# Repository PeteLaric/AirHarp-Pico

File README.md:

# AirHarp-Pico
A gestural autoharp that functions as a class-compliant USB MIDI controller instrument.

http://www.AirHarp.com

Originally conceived in 2010, the AirHarp is a gestural autoharp that allows the musician to strum chords on an invisible beam of ultrasound.  For several years, I manufactured and sold these musical instruments online.  The entire project is open source.  If you build one, please send me a note!  I'd love to see it.

Cheers,

~ Pete

http://www.PeteLaric.com

PeteLaric@protonmail.com

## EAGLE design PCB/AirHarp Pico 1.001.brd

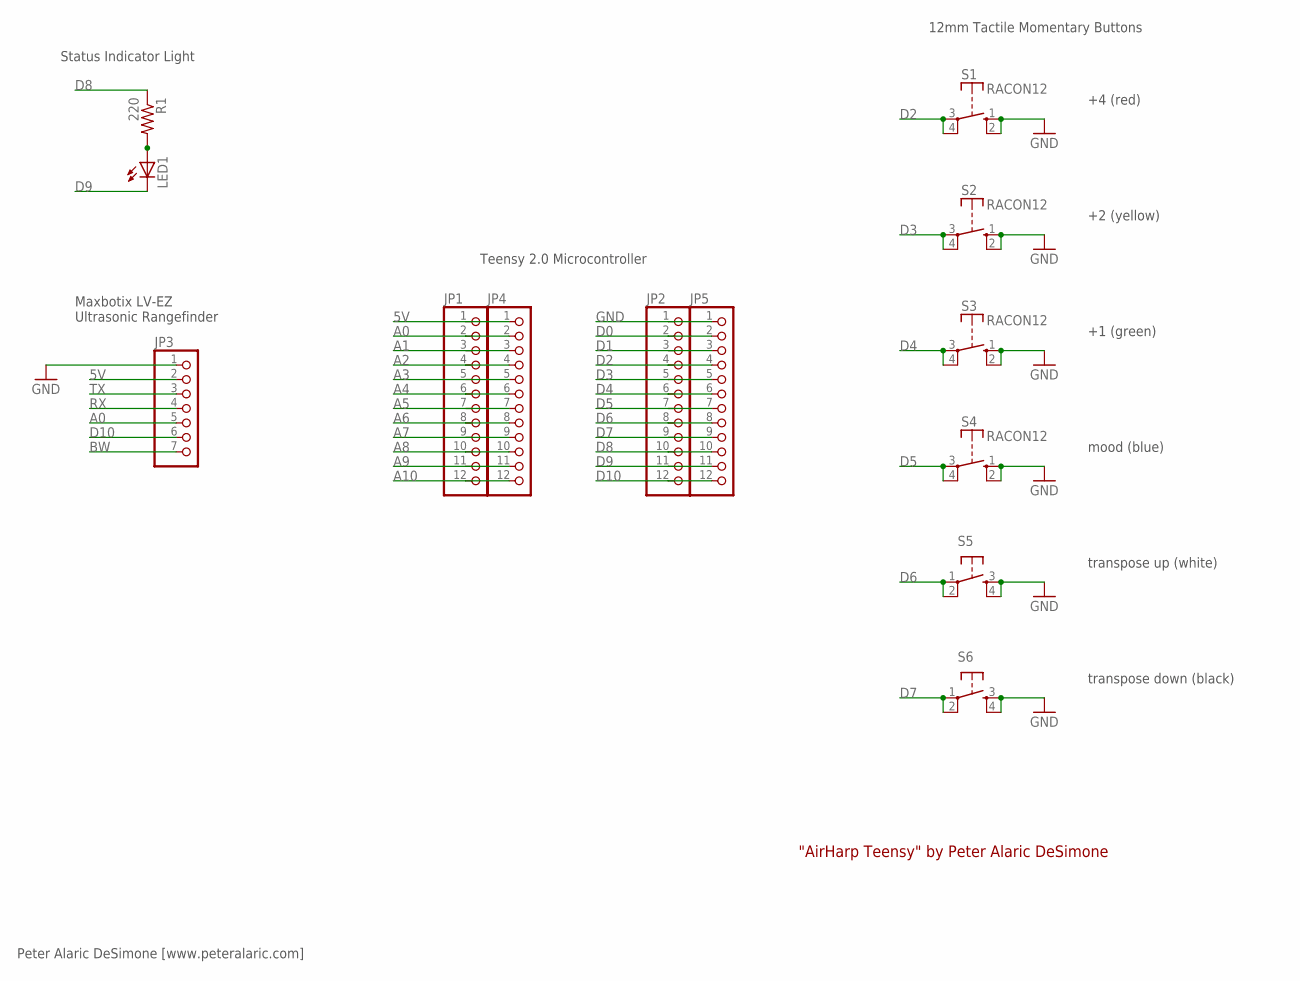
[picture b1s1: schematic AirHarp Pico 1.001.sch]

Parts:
JP1, JP2, JP4, JP5: PINHD-1X12; 1X12
JP3: PINHD-1X7; 1X07
LED1: LED10MM
R1: 220; 0207/7
S1, S2, S3, S4: RACON12
S5, S6: TAC_SWITCHPTH; TACTILE-PTH

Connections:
5V: JP1.1, JP3.2, JP4.1
A0: JP1.2, JP3.5, JP4.2
A1: JP1.3, JP4.3
A2: JP1.4, JP4.4
A3: JP1.5, JP4.5
A4: JP1.6, JP4.6
A5: JP1.7, JP4.7
A6: JP1.8, JP4.8
A7: JP1.9, JP4.9
A8: JP1.10, JP4.10
A9: JP1.11, JP4.11
A10: JP1.12, JP4.12
BW: JP3.7
D0: JP2.2, JP5.2
D1: JP2.3, JP5.3
D2: JP2.4, JP5.4, S1.3, S1.4
D3: JP2.5, JP5.5, S2.3, S2.4
D4: JP2.6, JP5.6, S3.3, S3.4
D5: JP2.7, JP5.7, S4.3, S4.4
D6: JP2.8, JP5.8, S5.1, S5.2
D7: JP2.9, JP5.9, S6.1, S6.2
D8: JP2.10, JP5.10, R1.1
D9: JP2.11, JP5.11, LED1.K (C)
D10: JP2.12, JP3.6, JP5.12
GND: JP2.1, JP3.1, JP5.1, S1.1 (S), S1.2 (S), S2.1 (S), S2.2 (S), S3.1 (S), S3.2 (S), S4.1 (S), S4.2 (S), S5.3, S5.4, S6.3, S6.4
unnamed: LED1.A, R1.2
RX: JP3.4
TX: JP3.3

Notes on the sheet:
"AirHarp Teensy" by Peter Alaric DeSimone
Peter Alaric DeSimone [www.peteralaric.com]
Maxbotix LV-EZ Ultrasonic Rangefinder
12mm Tactile Momentary Buttons
Teensy 2.0 Microcontroller
+4 (red)
+2 (yellow)
+1 (green)
mood (blue)
transpose up (white)
transpose down (black)
Status Indicator Light

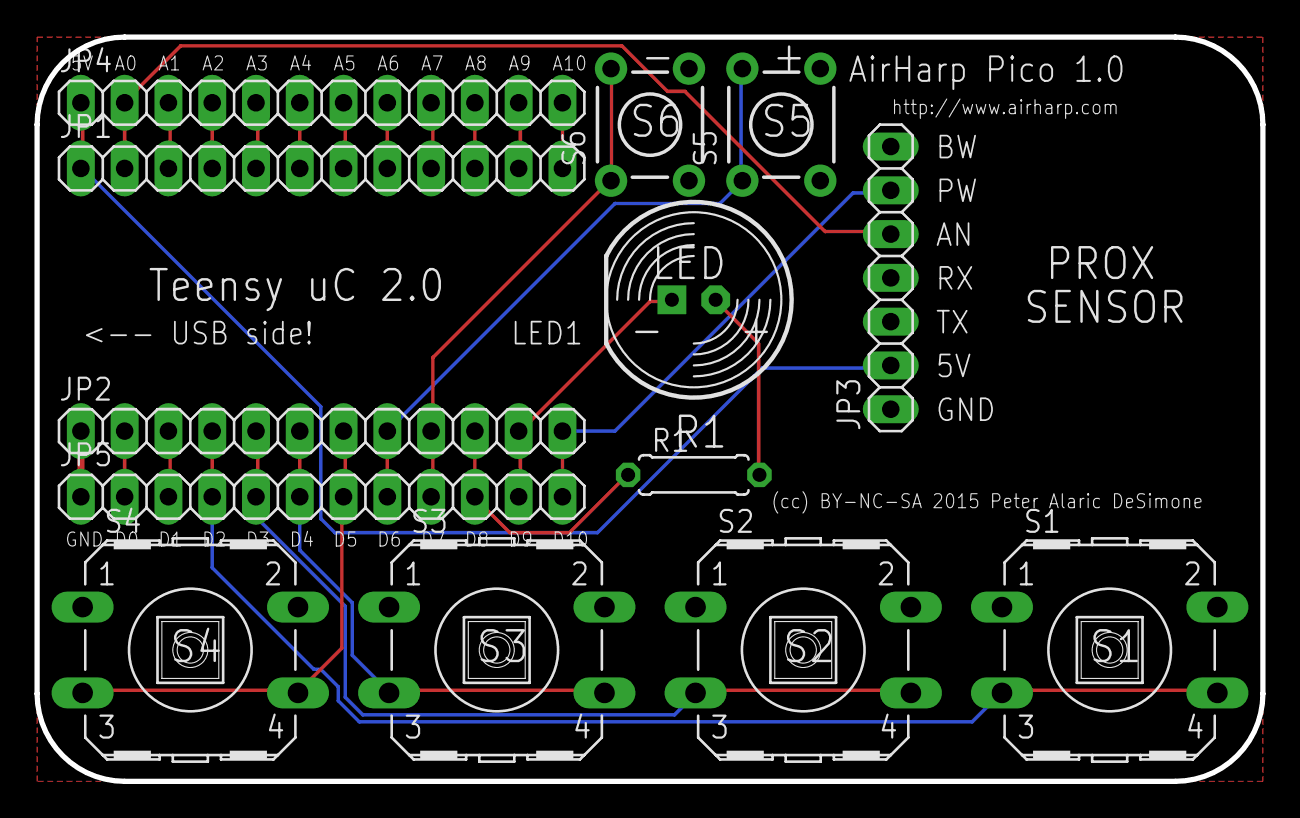
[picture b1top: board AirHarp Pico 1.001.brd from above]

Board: 2 copper layers, 71.1 x 43.2 mm, 13 parts (0 on the bottom side), 25 nets.

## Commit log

2021-03-22 Added 3D CAD for printable enclosure.
2021-03-22 Added firmware for Teensy 2.0 microcontroller.
2021-03-22 Added unit cost breakdown / bill of materials.
2021-03-22 Added printed circuit boards (PCBs).
2021-03-22 Added documentation.
2021-12-01 Added AirHarp Lira assembly manual
    Even though this manual is for the AirHarp Lira, not the AirHarp Pico, it may be of use to someone who is new to hobby electronics. Given the numerous similarities between the two devices, it may be 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

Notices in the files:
parts and their libraries:
SparkFun-Retired: Licensing:Creative Commons ShareAlike 4.0 International - https://creativecommons.org/licenses/by-sa/4.0
